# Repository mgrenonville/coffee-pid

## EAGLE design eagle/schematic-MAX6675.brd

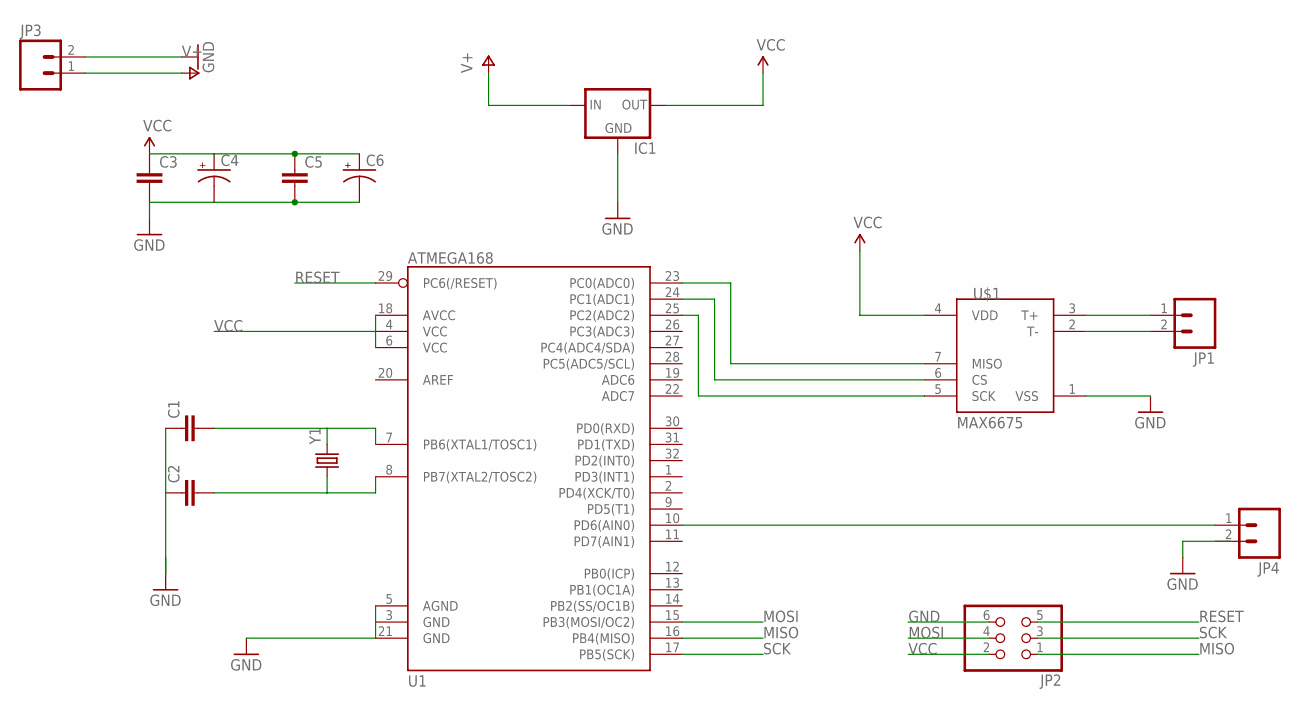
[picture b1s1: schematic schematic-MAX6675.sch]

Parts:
C1, C2: CAPPTH2; CAP-PTH-SMALL2
C3, C5: CAPPTH; CAP-PTH-SMALL
C4, C6: CAP_POLPTH2; CPOL-RADIAL-10UF-25V
IC1: V_REG_78XXSINK; TO220-IGO
JP1: M025MM; SCREWTERMINAL-5MM-2
JP2: PINHD-2X3; 2X03
JP3, JP4: M023.5MM_LOCK; SCREWTERMINAL-3.5MM-2_LOCK
U1: ATMEGA168; TQFP32-08
U$1: MAX6675; SO08-MAX6675
Y1: CRYSTALHC49US; HC49US

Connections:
GND: C1.1, C2.1, C3.2, C4.2 (-), C5.2, C6.2 (-), IC1.GND, JP2.6, JP3.2, U1.5 (AGND), U1.21 (GND), U$1.1 (VSS)
MISO: JP2.1, U1.16 (PB4(MISO))
MOSI: JP2.4, U1.15 (PB3(MOSI/OC2))
unnamed: JP1.1, U$1.3 (T+)
unnamed: C1.2, U1.7 (PB6(XTAL1/TOSC1)), Y1.2
unnamed: C2.2, U1.8 (PB7(XTAL2/TOSC2)), Y1.1
unnamed: JP1.2, U$1.2 (T-)
unnamed: U1.25 (PC2(ADC2)), U$1.5 (SCK)
unnamed: U1.24 (PC1(ADC1)), U$1.6 (CS)
unnamed: U1.23 (PC0(ADC0)), U$1.7 (MISO)
unnamed: JP4.1, U1.10 (PD6(AIN0))
RESET: JP2.5, U1.29 (PC6(/RESET))
SCK: JP2.3, U1.17 (PB5(SCK))
V+: IC1.IN, JP3.1
VCC: C3.1, C4.1 (+), C5.1, C6.1 (+), IC1.OUT, JP2.2, U1.4 (VCC), U1.6 (VCC), U1.18 (AVCC), U$1.4 (VDD)

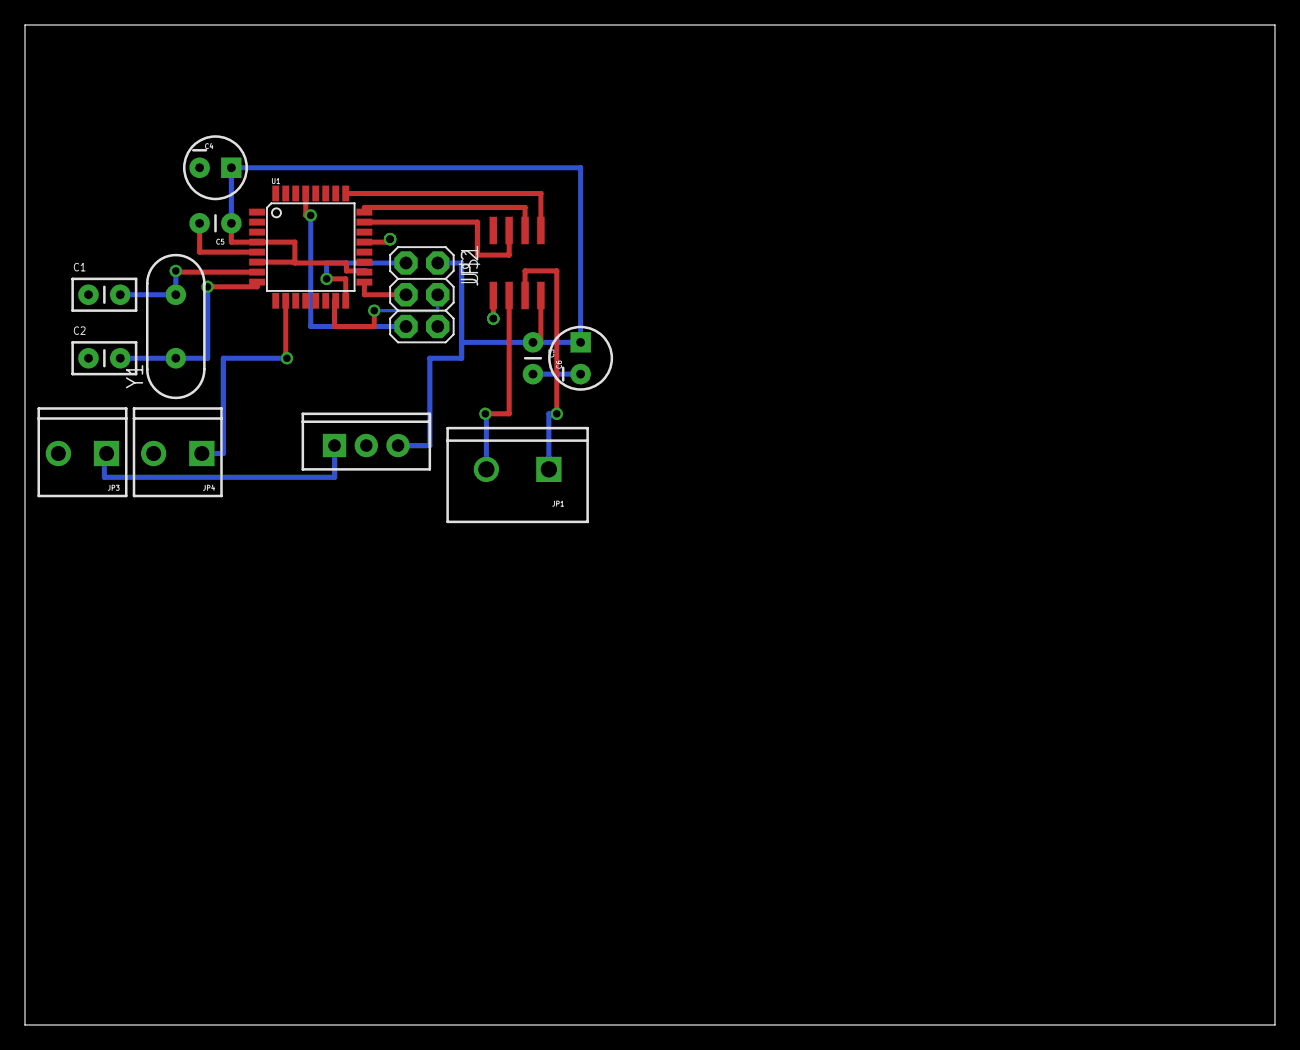
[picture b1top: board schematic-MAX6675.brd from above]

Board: 2 copper layers, 100.0 x 80.0 mm, 14 parts (0 on the bottom side), 15 nets.

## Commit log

2013-11-09 initial import
2013-11-25 improve temp measure
2013-11-25 eagles files

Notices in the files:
parts and their libraries:
SparkFun: Licensing: CC v3.0 Share-Alike You are welcome to use this library for commercial purposes.
